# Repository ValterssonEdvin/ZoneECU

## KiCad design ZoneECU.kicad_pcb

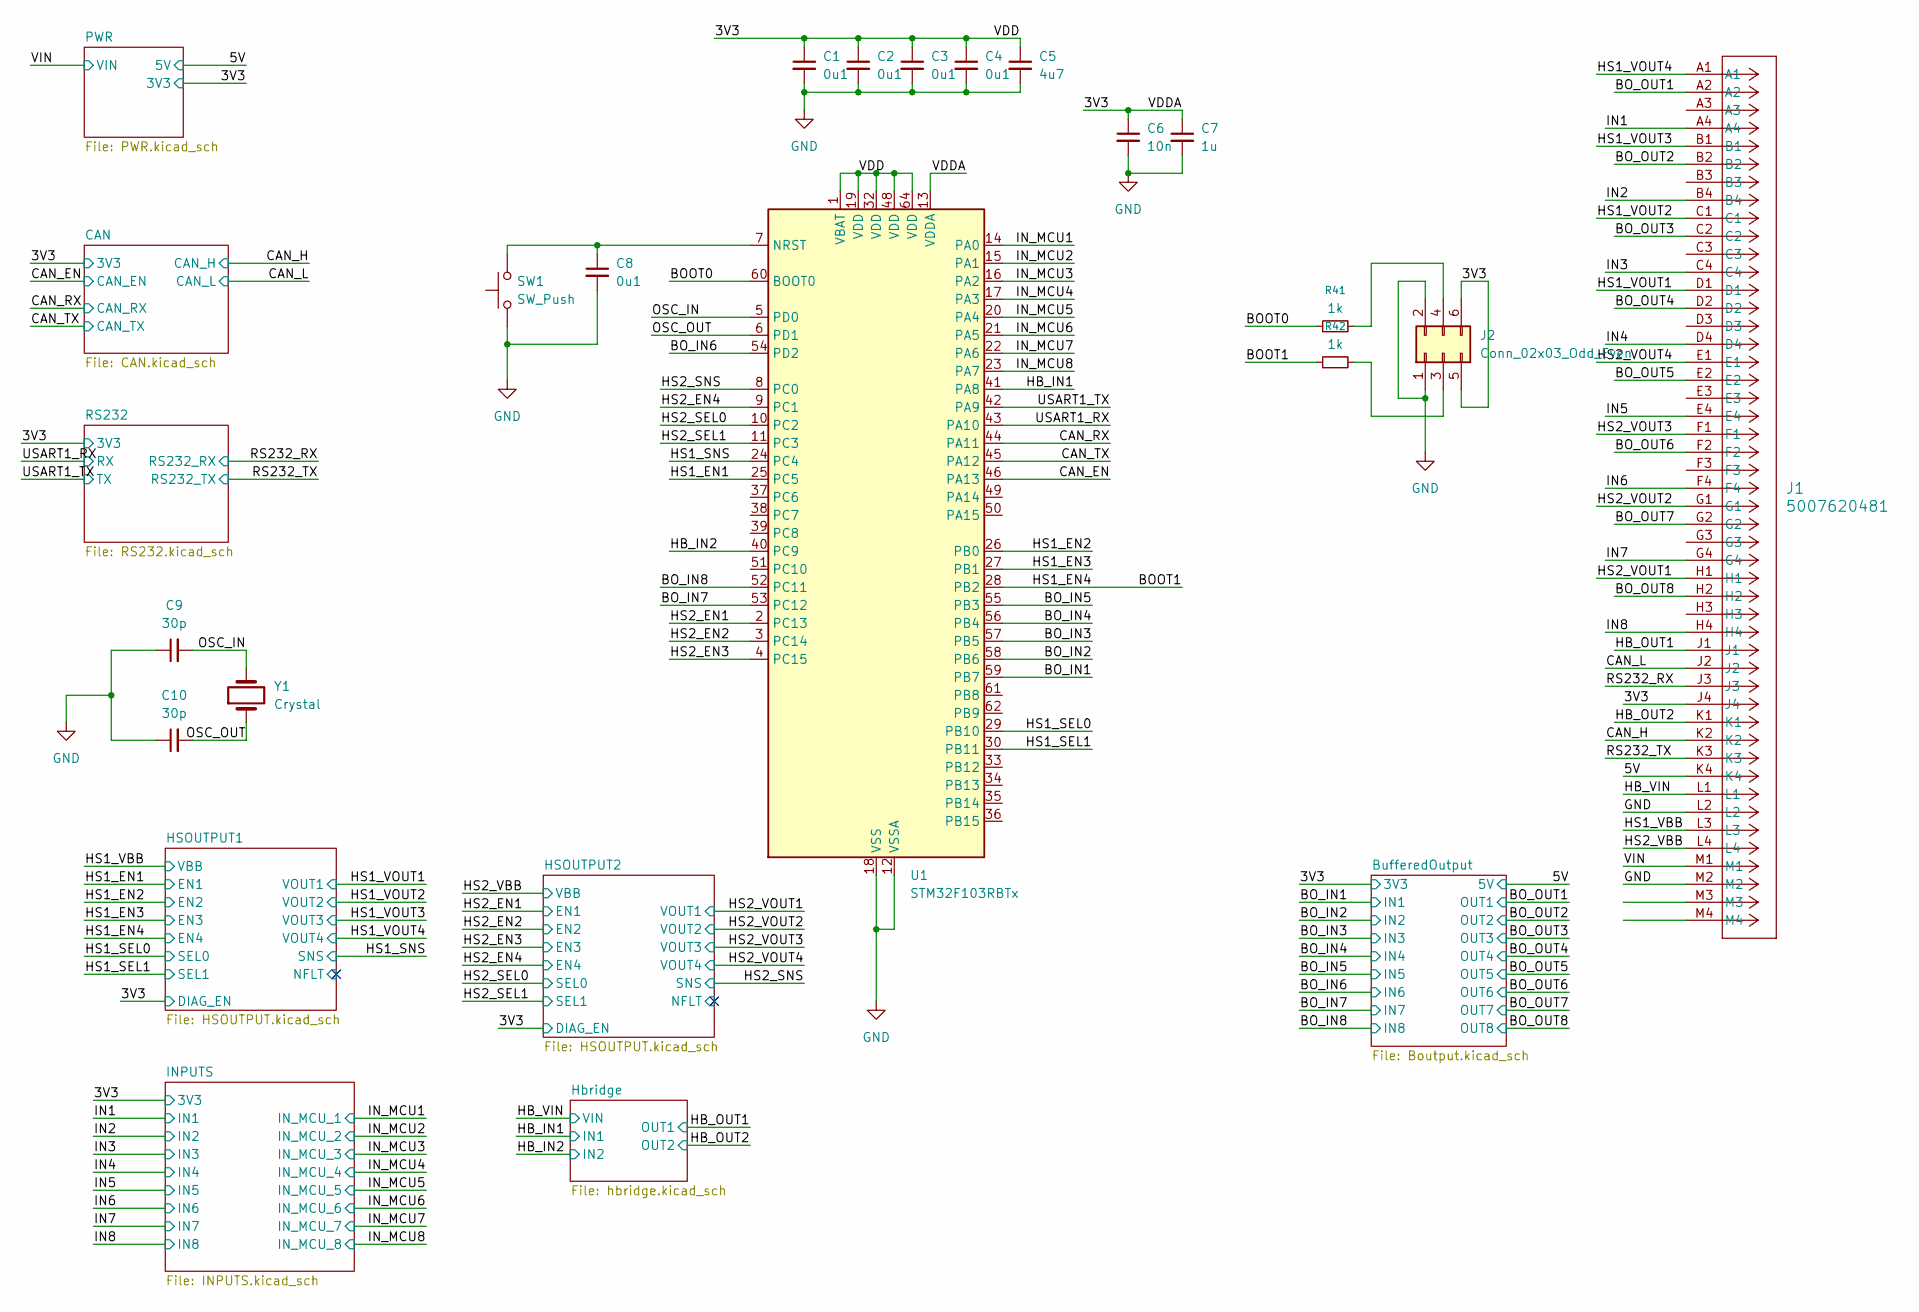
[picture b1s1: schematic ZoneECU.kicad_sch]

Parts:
C1, C2, C3, C4, C8: 0u1; C_0603_1608Metric_Pad1.08x0.95mm_HandSolder
C5: 4u7; C_0603_1608Metric_Pad1.08x0.95mm_HandSolder
C6: 10n; C_0603_1608Metric_Pad1.08x0.95mm_HandSolder
C7: 1u; C_0603_1608Metric_Pad1.08x0.95mm_HandSolder
C9, C10: 30p; C_0603_1608Metric_Pad1.08x0.95mm_HandSolder
J1: 5007620481; CONN_SD-500762-001_MOL
J2: Conn_02x03_Odd_Even; PinHeader_2x03_P2.54mm_Vertical
R41, R42: 1k; R_0603_1608Metric_Pad0.98x0.95mm_HandSolder
SW1: SW_Push; SW_SPST_B3S-1000
U1: STM32F103RBTx; LQFP-64_10x10mm_P0.5mm
Y1: Crystal; Crystal_SMD_HC49-SD_HandSoldering

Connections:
/3V3: C1.1, C2.1, C3.1, C4.1, C5.1, C6.1, C7.1, J1.J4, J2.5, J2.6, U1.1 (VBAT), U1.13 (VDDA), U1.19 (VDD), U1.32 (VDD), U1.48 (VDD), U1.64 (VDD); also elsewhere on the board
/5V: J1.K4; also elsewhere on the board
/BOOT0: R41.1, U1.60 (BOOT0)
/BOOT1: R42.1, U1.28 (PB2); also elsewhere on the board
/BO_IN1: U1.59 (PB7); also elsewhere on the board
/BO_IN2: U1.58 (PB6); also elsewhere on the board
/BO_IN3: U1.57 (PB5); also elsewhere on the board
/BO_IN4: U1.56 (PB4); also elsewhere on the board
/BO_IN5: U1.55 (PB3); also elsewhere on the board
/BO_IN6: U1.54 (PD2); also elsewhere on the board
/BO_IN7: U1.53 (PC12); also elsewhere on the board
/BO_IN8: U1.52 (PC11); also elsewhere on the board
/BO_OUT1: J1.A2; also elsewhere on the board
/BO_OUT2: J1.B2; also elsewhere on the board
/BO_OUT3: J1.C2; also elsewhere on the board
/BO_OUT4: J1.D2; also elsewhere on the board
/BO_OUT5: J1.E2; also elsewhere on the board
/BO_OUT6: J1.F2; also elsewhere on the board
/BO_OUT7: J1.G2; also elsewhere on the board
/BO_OUT8: J1.H2; also elsewhere on the board
/CAN_EN: U1.46 (PA13); also elsewhere on the board
/CAN_H: J1.K2; also elsewhere on the board
/CAN_L: J1.J2; also elsewhere on the board
/CAN_RX: U1.44 (PA11); also elsewhere on the board
/CAN_TX: U1.45 (PA12); also elsewhere on the board
/HB_IN1: U1.41 (PA8); also elsewhere on the board
/HB_IN2: U1.40 (PC9); also elsewhere on the board
/HB_OUT1: J1.J1; also elsewhere on the board
/HB_OUT2: J1.K1; also elsewhere on the board
/HB_VIN: J1.L1; also elsewhere on the board
/HS1_EN1: U1.25 (PC5); also elsewhere on the board
/HS1_EN2: U1.26 (PB0); also elsewhere on the board
/HS1_EN3: U1.27 (PB1); also elsewhere on the board
/HS1_SEL0: U1.29 (PB10); also elsewhere on the board
/HS1_SEL1: U1.30 (PB11); also elsewhere on the board
/HS1_SNS: U1.24 (PC4); also elsewhere on the board
/HS1_VBB: J1.L3; also elsewhere on the board
/HS1_VOUT1: J1.D1; also elsewhere on the board
/HS1_VOUT2: J1.C1; also elsewhere on the board
/HS1_VOUT3: J1.B1; also elsewhere on the board
/HS1_VOUT4: J1.A1; also elsewhere on the board
/HS2_EN1: U1.2 (PC13); also elsewhere on the board
/HS2_EN2: U1.3 (PC14); also elsewhere on the board
/HS2_EN3: U1.4 (PC15); also elsewhere on the board
/HS2_EN4: U1.9 (PC1); also elsewhere on the board
/HS2_SEL0: U1.10 (PC2); also elsewhere on the board
/HS2_SEL1: U1.11 (PC3); also elsewhere on the board
/HS2_SNS: U1.8 (PC0); also elsewhere on the board
/HS2_VBB: J1.L4; also elsewhere on the board
/HS2_VOUT1: J1.H1; also elsewhere on the board
/HS2_VOUT2: J1.G1; also elsewhere on the board
/HS2_VOUT3: J1.F1; also elsewhere on the board
/HS2_VOUT4: J1.E1; also elsewhere on the board
/IN1: J1.A4; also elsewhere on the board
/IN2: J1.B4; also elsewhere on the board
/IN3: J1.C4; also elsewhere on the board
/IN4: J1.D4; also elsewhere on the board
/IN5: J1.E4; also elsewhere on the board
/IN6: J1.F4; also elsewhere on the board
/IN7: J1.G4; also elsewhere on the board
/IN8: J1.H4; also elsewhere on the board
/IN_MCU1: U1.14 (PA0); also elsewhere on the board
/IN_MCU2: U1.15 (PA1); also elsewhere on the board
/IN_MCU3: U1.16 (PA2); also elsewhere on the board
/IN_MCU4: U1.17 (PA3); also elsewhere on the board
/IN_MCU5: U1.20 (PA4); also elsewhere on the board
/IN_MCU6: U1.21 (PA5); also elsewhere on the board
/IN_MCU7: U1.22 (PA6); also elsewhere on the board
/IN_MCU8: U1.23 (PA7); also elsewhere on the board
/OSC_IN: C9.2, U1.5 (PD0), Y1.2
/OSC_OUT: C10.2, U1.6 (PD1), Y1.1
/RS232_RX: J1.J3; also elsewhere on the board
/RS232_TX: J1.K3; also elsewhere on the board
/USART1_RX: U1.43 (PA10); also elsewhere on the board
/USART1_TX: U1.42 (PA9); also elsewhere on the board
/VIN: J1.M1; also elsewhere on the board
GND: C1.2, C2.2, C3.2, C4.2, C5.2, C6.2, C7.2, C8.2, C9.1, C10.1, J1.L2, J1.M2, J2.1, J2.2, SW1.1, U1.12 (VSSA), U1.18 (VSS), U1.31 (VSS), U1.47 (VSS), U1.63 (VSS); also elsewhere on the board
unnamed: J2.3, R42.2
unnamed: J2.4, R41.2
unnamed: C8.1, SW1.2, U1.7 (NRST)

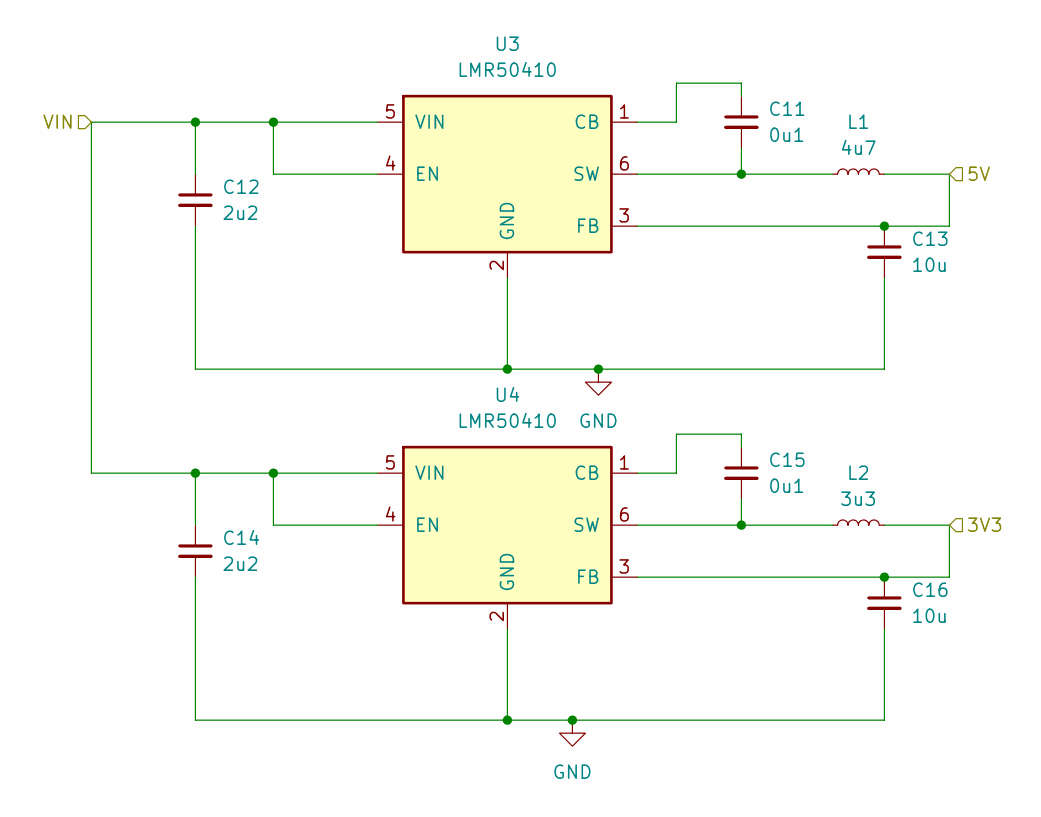
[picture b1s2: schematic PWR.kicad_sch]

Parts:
C11, C15: 0u1; C_0603_1608Metric_Pad1.08x0.95mm_HandSolder
C12, C14: 2u2; C_0603_1608Metric_Pad1.08x0.95mm_HandSolder
C13, C16: 10u; C_0603_1608Metric_Pad1.08x0.95mm_HandSolder
L1: 4u7; L_0603_1608Metric_Pad1.05x0.95mm_HandSolder
L2: 3u3; L_0603_1608Metric_Pad1.05x0.95mm_HandSolder
U3, U4: LMR50410; SOT-23-6

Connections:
/3V3: C16.1, L2.2, U4.3 (FB); also elsewhere on the board
/5V: C13.1, L1.2, U3.3 (FB); also elsewhere on the board
/VIN: C12.1, C14.1, U3.4 (EN), U3.5 (VIN), U4.4 (EN), U4.5 (VIN); also elsewhere on the board
GND: C12.2, C13.2, C14.2, C16.2, U3.2 (GND), U4.2 (GND); also elsewhere on the board
unnamed: C11.1, U3.1 (CB)
unnamed: C11.2, L1.1, U3.6 (SW)
unnamed: C15.1, U4.1 (CB)
unnamed: C15.2, L2.1, U4.6 (SW)

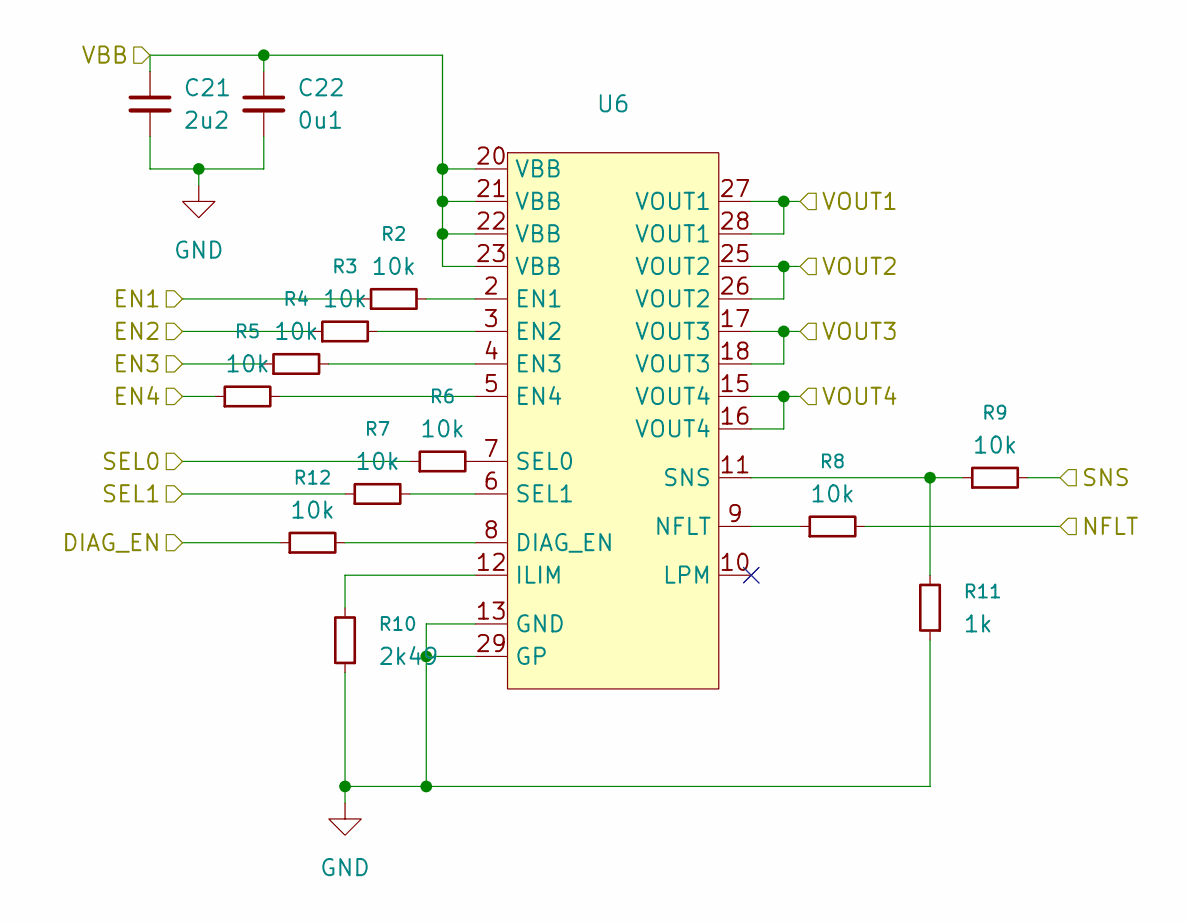
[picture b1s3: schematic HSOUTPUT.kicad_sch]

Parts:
C21: 2u2; C_0603_1608Metric_Pad1.08x0.95mm_HandSolder
C22: 0u1; C_0603_1608Metric_Pad1.08x0.95mm_HandSolder
R2, R3, R4, R5, R6, R7, R8, R9, R12: 10k; R_0603_1608Metric_Pad0.98x0.95mm_HandSolder
R10: 2k49; R_0603_1608Metric_Pad0.98x0.95mm_HandSolder
R11: 1k; R_0603_1608Metric_Pad0.98x0.95mm_HandSolder
U6: HVSSOP-28-1EP_3x7.1mm_P0.5mm_EP1.57x1.88mm_ThermalVias

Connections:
/3V3: R12.1; also elsewhere on the board
/BOOT1: R5.1; also elsewhere on the board
/HS1_EN1: R2.1; also elsewhere on the board
/HS1_EN2: R3.1; also elsewhere on the board
/HS1_EN3: R4.1; also elsewhere on the board
/HS1_SEL0: R6.1; also elsewhere on the board
/HS1_SEL1: R7.1; also elsewhere on the board
/HS1_SNS: R9.2; also elsewhere on the board
/HS1_VBB: C21.1, C22.1, U6.20 (VBB), U6.21 (VBB), U6.22 (VBB), U6.23 (VBB); also elsewhere on the board
/HS1_VOUT1: U6.27 (VOUT1), U6.28 (VOUT1); also elsewhere on the board
/HS1_VOUT2: U6.25 (VOUT2), U6.26 (VOUT2); also elsewhere on the board
/HS1_VOUT3: U6.17 (VOUT3), U6.18 (VOUT3); also elsewhere on the board
/HS1_VOUT4: U6.15 (VOUT4), U6.16 (VOUT4); also elsewhere on the board
/HSOUTPUT1/NFLT: R8.2
GND: C21.2, C22.2, R10.1, R11.1, U6.13 (GND), U6.29 (GP); also elsewhere on the board
unnamed: R12.2, U6.8 (DIAG_EN)
unnamed: R2.2, U6.2 (EN1)
unnamed: R3.2, U6.3 (EN2)
unnamed: R4.2, U6.4 (EN3)
unnamed: R5.2, U6.5 (EN4)
unnamed: R10.2, U6.12 (ILIM)
unnamed: R8.1, U6.9 (NFLT)
unnamed: R6.2, U6.7 (SEL0)
unnamed: R7.2, U6.6 (SEL1)
unnamed: R9.1, R11.2, U6.11 (SNS)

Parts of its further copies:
C25: 2u2; C_0603_1608Metric_Pad1.08x0.95mm_HandSolder
C26: 0u1; C_0603_1608Metric_Pad1.08x0.95mm_HandSolder
R30, R31, R32, R33, R35, R36, R37, R38, R40: 10k; R_0603_1608Metric_Pad0.98x0.95mm_HandSolder
R34: 2k49; R_0603_1608Metric_Pad0.98x0.95mm_HandSolder
R39: 1k; R_0603_1608Metric_Pad0.98x0.95mm_HandSolder
U8: HVSSOP-28-1EP_3x7.1mm_P0.5mm_EP1.57x1.88mm_ThermalVias

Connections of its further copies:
/3V3: R32.1; also elsewhere on the board
/HS2_EN1: R36.1; also elsewhere on the board
/HS2_EN2: R33.1; also elsewhere on the board
/HS2_EN3: R31.1; also elsewhere on the board
/HS2_EN4: R30.1; also elsewhere on the board
/HS2_SEL0: R37.1; also elsewhere on the board
/HS2_SEL1: R35.1; also elsewhere on the board
/HS2_SNS: R40.2; also elsewhere on the board
/HS2_VBB: C25.1, C26.1, U8.20 (VBB), U8.21 (VBB), U8.22 (VBB), U8.23 (VBB); also elsewhere on the board
/HS2_VOUT1: U8.27 (VOUT1), U8.28 (VOUT1); also elsewhere on the board
/HS2_VOUT2: U8.25 (VOUT2), U8.26 (VOUT2); also elsewhere on the board
/HS2_VOUT3: U8.17 (VOUT3), U8.18 (VOUT3); also elsewhere on the board
/HS2_VOUT4: U8.15 (VOUT4), U8.16 (VOUT4); also elsewhere on the board
/HSOUTPUT2/NFLT: R38.2
GND: C25.2, C26.2, R34.1, R39.1, U8.13 (GND), U8.29 (GP); also elsewhere on the board
unnamed: R32.2, U8.8 (DIAG_EN)
unnamed: R36.2, U8.2 (EN1)
unnamed: R33.2, U8.3 (EN2)
unnamed: R31.2, U8.4 (EN3)
unnamed: R30.2, U8.5 (EN4)
unnamed: R34.2, U8.12 (ILIM)
unnamed: R38.1, U8.9 (NFLT)
unnamed: R37.2, U8.7 (SEL0)
unnamed: R35.2, U8.6 (SEL1)
unnamed: R39.2, R40.1, U8.11 (SNS)

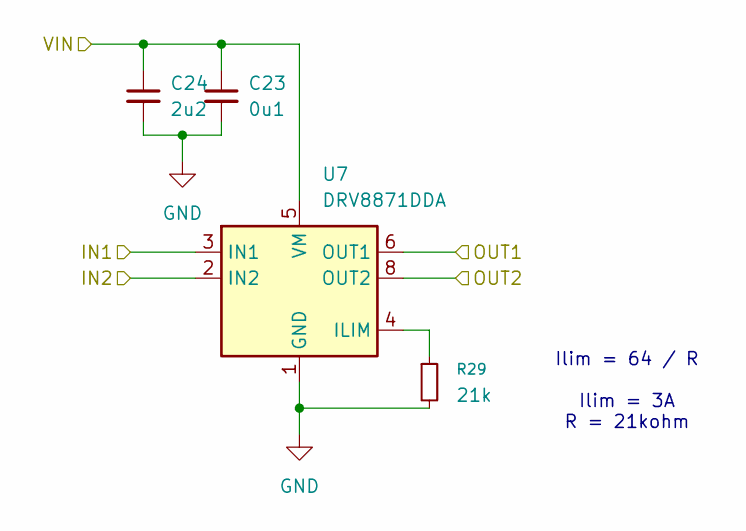
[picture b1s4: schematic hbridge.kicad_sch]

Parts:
C23: 0u1; C_0603_1608Metric_Pad1.08x0.95mm_HandSolder
C24: 2u2; C_0603_1608Metric_Pad1.08x0.95mm_HandSolder
R29: 21k; R_0603_1608Metric_Pad0.98x0.95mm_HandSolder
U7: DRV8871DDA; Texas_HTSOP-8-1EP_3.9x4.9mm_P1.27mm_EP2.95x4.9mm_Mask2.4x3.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

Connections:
/HB_IN1: U7.3 (IN1); also elsewhere on the board
/HB_IN2: U7.2 (IN2); also elsewhere on the board
/HB_OUT1: U7.6 (OUT1); also elsewhere on the board
/HB_OUT2: U7.8 (OUT2); also elsewhere on the board
/HB_VIN: C23.1, C24.1, U7.5 (VM); also elsewhere on the board
GND: C23.2, C24.2, R29.2, U7.1 (GND), U7.7 (GND), U7.9 (GND); also elsewhere on the board
unnamed: R29.1, U7.4 (ILIM)

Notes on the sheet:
Ilim = 64 / R Ilim = 3A R = 21kohm

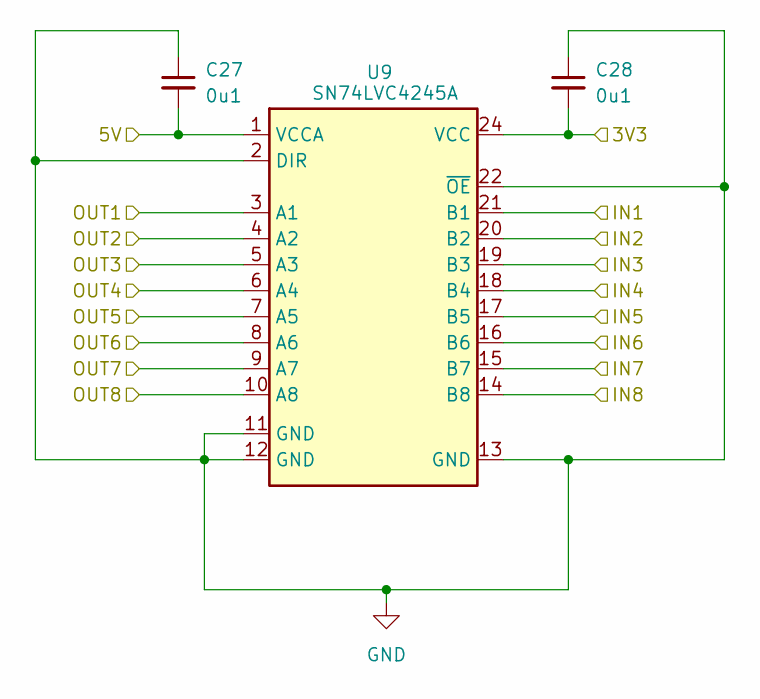
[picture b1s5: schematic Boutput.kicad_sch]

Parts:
C27, C28: 0u1; C_0603_1608Metric_Pad1.08x0.95mm_HandSolder
U9: SN74LVC4245A; TSSOP-24_4.4x7.8mm_P0.65mm

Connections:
/3V3: C28.2, U9.24 (VCC); also elsewhere on the board
/5V: C27.2, U9.1 (VCCA); also elsewhere on the board
/BO_IN1: U9.21 (B1); also elsewhere on the board
/BO_IN2: U9.20 (B2); also elsewhere on the board
/BO_IN3: U9.19 (B3); also elsewhere on the board
/BO_IN4: U9.18 (B4); also elsewhere on the board
/BO_IN5: U9.17 (B5); also elsewhere on the board
/BO_IN6: U9.16 (B6); also elsewhere on the board
/BO_IN7: U9.15 (B7); also elsewhere on the board
/BO_IN8: U9.14 (B8); also elsewhere on the board
/BO_OUT1: U9.3 (A1); also elsewhere on the board
/BO_OUT2: U9.4 (A2); also elsewhere on the board
/BO_OUT3: U9.5 (A3); also elsewhere on the board
/BO_OUT4: U9.6 (A4); also elsewhere on the board
/BO_OUT5: U9.7 (A5); also elsewhere on the board
/BO_OUT6: U9.8 (A6); also elsewhere on the board
/BO_OUT7: U9.9 (A7); also elsewhere on the board
/BO_OUT8: U9.10 (A8); also elsewhere on the board
GND: C27.1, C28.1, U9.2 (DIR), U9.11 (GND), U9.12 (GND), U9.13 (GND), U9.22 (~OE); also elsewhere on the board

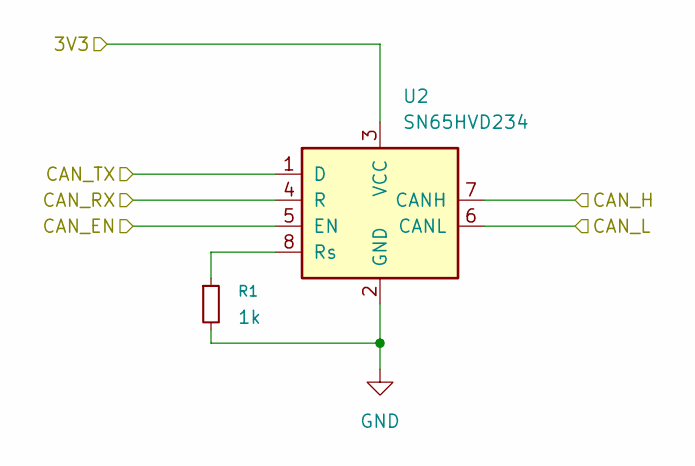
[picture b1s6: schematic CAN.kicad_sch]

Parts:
R1: 1k; R_0603_1608Metric_Pad0.98x0.95mm_HandSolder
U2: SN65HVD234; SOIC-8_3.9x4.9mm_P1.27mm

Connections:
/3V3: U2.3 (VCC); also elsewhere on the board
/CAN_EN: U2.5 (EN); also elsewhere on the board
/CAN_H: U2.7 (CANH); also elsewhere on the board
/CAN_L: U2.6 (CANL); also elsewhere on the board
/CAN_RX: U2.4 (R); also elsewhere on the board
/CAN_TX: U2.1 (D); also elsewhere on the board
GND: R1.2, U2.2 (GND); also elsewhere on the board
unnamed: R1.1, U2.8 (Rs)

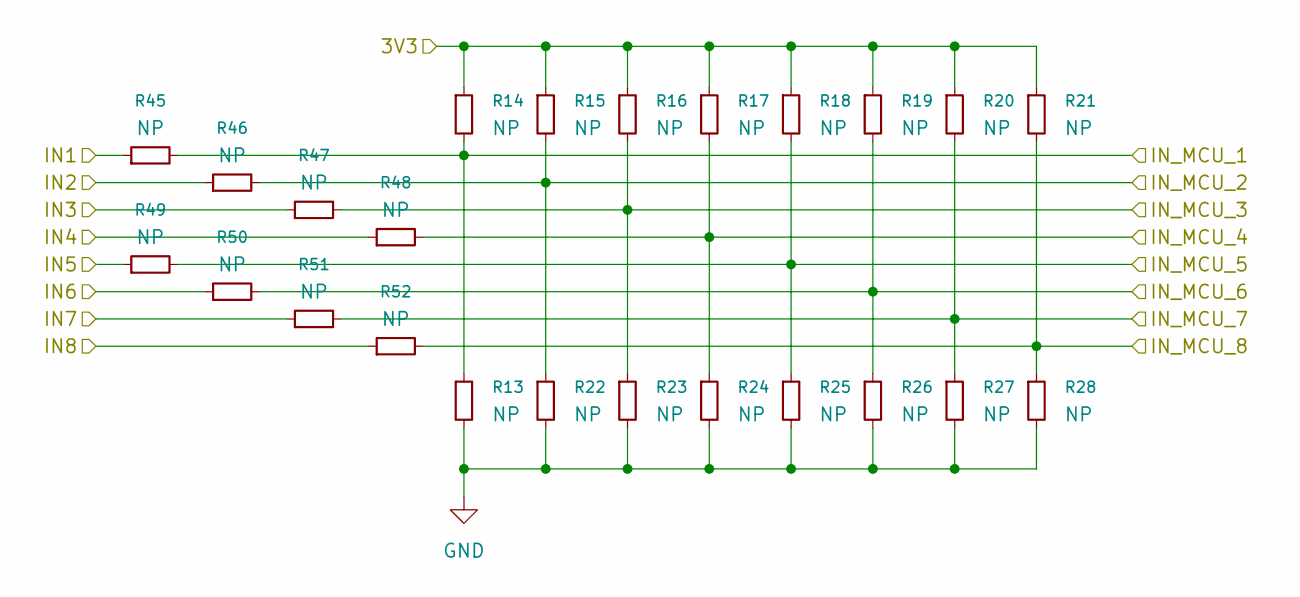
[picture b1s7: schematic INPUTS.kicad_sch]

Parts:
R13, R14, R15, R16, R17, R18, R19, R20, R21, R22, R23, R24, R25, R26, R27, R28, R45, R46, R47, R48, R49, R50, R51, R52: NP; R_0603_1608Metric_Pad0.98x0.95mm_HandSolder

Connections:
/3V3: R14.1, R15.1, R16.1, R17.1, R18.1, R19.1, R20.1, R21.1; also elsewhere on the board
/IN1: R45.1; also elsewhere on the board
/IN2: R46.1; also elsewhere on the board
/IN3: R47.1; also elsewhere on the board
/IN4: R48.1; also elsewhere on the board
/IN5: R49.1; also elsewhere on the board
/IN6: R50.1; also elsewhere on the board
/IN7: R51.1; also elsewhere on the board
/IN8: R52.1; also elsewhere on the board
/IN_MCU1: R13.1, R14.2, R45.2; also elsewhere on the board
/IN_MCU2: R15.2, R22.1, R46.2; also elsewhere on the board
/IN_MCU3: R16.2, R23.1, R47.2; also elsewhere on the board
/IN_MCU4: R17.2, R24.1, R48.2; also elsewhere on the board
/IN_MCU5: R18.2, R25.1, R49.2; also elsewhere on the board
/IN_MCU6: R19.2, R26.1, R50.2; also elsewhere on the board
/IN_MCU7: R20.2, R27.1, R51.2; also elsewhere on the board
/IN_MCU8: R21.2, R28.1, R52.2; also elsewhere on the board
GND: R13.2, R22.2, R23.2, R24.2, R25.2, R26.2, R27.2, R28.2; also elsewhere on the board

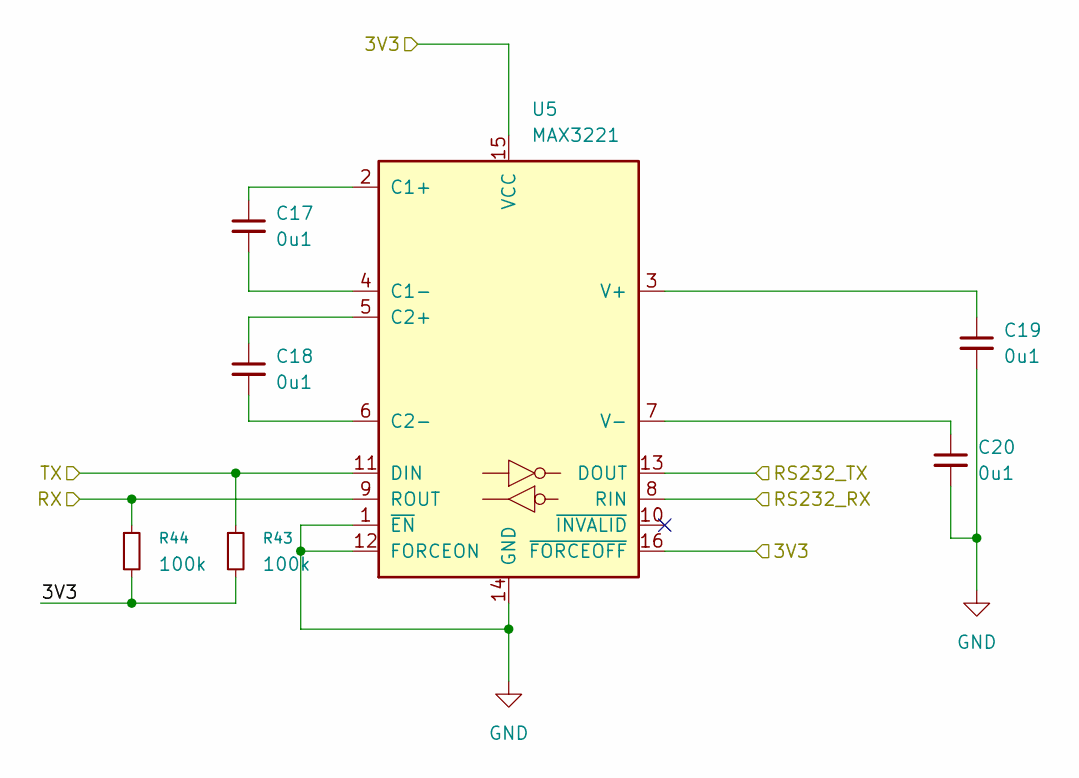
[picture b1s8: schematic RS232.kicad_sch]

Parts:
C17, C18, C19, C20: 0u1; C_0603_1608Metric_Pad1.08x0.95mm_HandSolder
R43, R44: 100k; R_0603_1608Metric_Pad0.98x0.95mm_HandSolder
U5: MAX3221; TSSOP-16_4.4x5mm_P0.65mm

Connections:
/3V3: R43.2, R44.2, U5.15 (VCC), U5.16 (~FORCEOFF); also elsewhere on the board
/RS232_RX: U5.8 (RIN); also elsewhere on the board
/RS232_TX: U5.13 (DOUT); also elsewhere on the board
/USART1_RX: R44.1, U5.9 (ROUT); also elsewhere on the board
/USART1_TX: R43.1, U5.11 (DIN); also elsewhere on the board
GND: C19.2, C20.2, U5.1 (~EN), U5.12 (FORCEON), U5.14 (GND); also elsewhere on the board
unnamed: C17.1, U5.2 (C1+)
unnamed: C17.2, U5.4 (C1-)
unnamed: C18.1, U5.5 (C2+)
unnamed: C18.2, U5.6 (C2-)
unnamed: C19.1, U5.3 (V+)
unnamed: C20.1, U5.7 (V-)

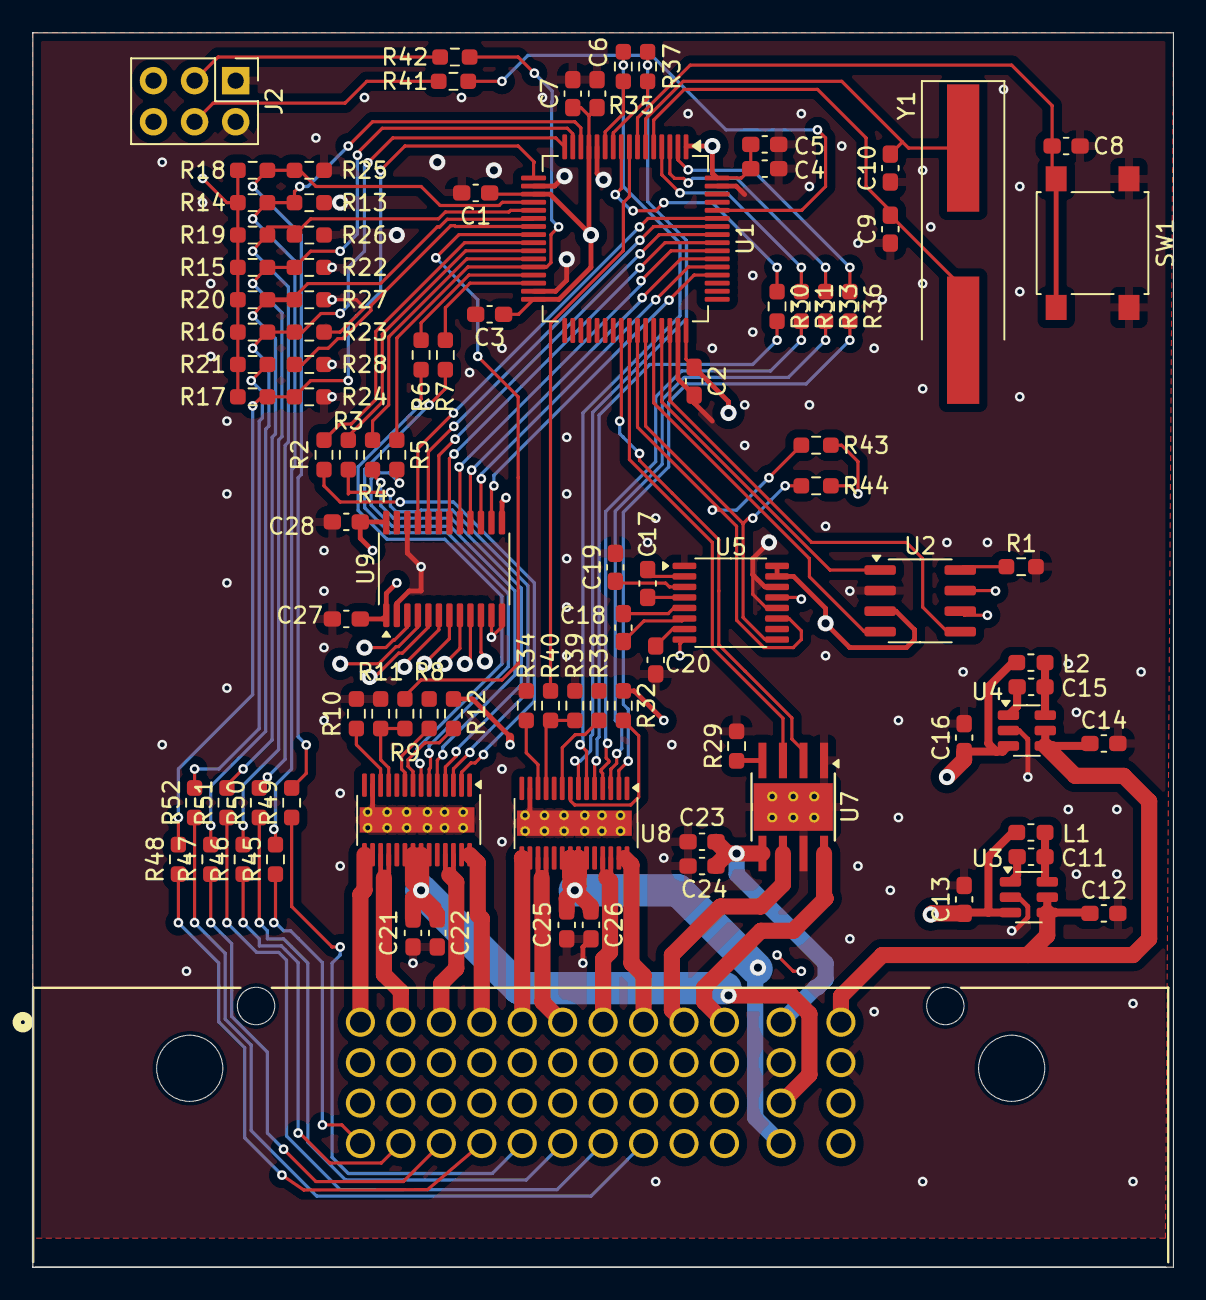
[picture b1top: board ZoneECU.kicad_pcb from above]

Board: 4 copper layers, 70.5 x 76.3 mm, 95 parts (0 on the bottom side), 112 nets.

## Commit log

2025-11-07 First version
2025-11-07 Swapped USART1 RX/TX, added pull ups for USART lines
2025-11-07 Add serial resistors on input pins
